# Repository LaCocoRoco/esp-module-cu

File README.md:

# Control Unit

Receiver to control onbaoard relays.

## Quick Guide

1. Order PCB by uploading the [Gerber File](pcb/cam/esp-module-cu.zip) to [JLCPCB](https://jlcpcb.com/).
2. Order Parts by uploading the [BOM File](pcb/bom/esp-module-cu.csv) to [LCSC](https://www.lcsc.com/bom).
3. Build PCB by placing components as visualized in the [BOM Viewer](https://htmlpreview.github.io/?https://github.com/LaCocoRoco/esp-module-cu/blob/main/pcb/bom/esp-module-cu.html).
4. Download & Install [Git](https://git-scm.com/), [CP210x Driver](https://www.silabs.com/developers/usb-to-uart-bridge-vcp-drivers?tab=downloads) and [VSCode](https://code.visualstudio.com/) with [PlatformIO](https://platformio.org/) Extension.
5. Clone the Repository `git clone --recursive https://github.com/LaCocoRoco/esp-module-cu.git`.
6. Customize your desired behaviour in [io.cpp](https://github.com/LaCocoRoco/esp-module-codebase/blob/main/src/io.cpp) or use the existing code from the [home](https://github.com/LaCocoRoco/esp-module-codebase/tree/home) branche.
7. With PlatformIO `Upload Filsystem Image` & `Upload & Monitor ` to your board.

## Module Modes

Modes can be changed by pressing the mode button.  
An audio signal will provide feedback for the active mode.  
Holding the mode button for more than two seconds will clear the module.

### Low Power Mode

- Feedback with one audio signal
- All web functionality is disabled
- Device will enter deep sleep when inactive
- Battery lifetime of several months

### Hybrid Mode

- Feedback with two audio signals
- All web functionality is disabled
- Device will enter deep sleep when battery voltage is below 3.8V
- Battery lifetime of several days

### Web Mode

- Feedback with three audio signals
- All web functionality is enabled
- Battery lifetime of several hours

## Importend

All modules have three different modes: Web Mode, Hybrid Mode, and Low Power Mode.  
The Wi-Fi can be configured as either Access Point or Station Mode.  
However, due to the use of the EspNow protocol for communication, there are some restrictions.

### Modules Set Up as Access Points (Default):

- All modes work without any restrictions.

### Modules Set Up in Station Mode:

- Web Mode works without any restrictions.
- Low Power Mode and Hybrid Mode only work if the Wi-Fi network is set to a **fixed channel**.

### Modules Set Up in Access Point or Station Mode:

- All modes only work if the Wi-Fi network is set to **channel 1**.

## Explanation

The main goal of this project was to avoid reliance on any infrastructure. For configuration, neither an application nor an existing Wi-Fi network is necessary. All modules can be accessed via the corresponding SSID in Access Point Mode or via hostname in Station Mode. However, there are some trade-offs:

To reduce power consumption in Low Power Mode, the module does not establish a direct network connection. It only broadcasts data to the specified receiver. In Station Mode, the network may change the Wi-Fi channel occasionally. Connecting to the network to receive this information would significantly increase uptime.

An alternative approach to this problem would be to scan for the receiver and request the channel. However, this has additional drawbacks:

- Scanning for this information takes some time (though less compared to connecting to a Wi-Fi network).
- It is difficult to distinguish whether a transmission failure is due to the wrong channel or a general network issue.
- Continuously requesting this information until a response is received would quickly add to the uptime and increase power consumption.

This is the reason why the relevant points must be considered mentioned in the [Importand](#importend) section.

## Reference

- [VSCode](https://code.visualstudio.com/) - Lightweight code editor.
- [PlatformIO](https://platformio.org/) - Embedded software development gateway.
- [Autodesk Fusion 360](https://www.autodesk.com/products/fusion-360) - Design and manufacturing software for CAD, CAM, CAE, and PCB.
- [Autodesk Eagle](https://www.autodesk.com/products/eagle) - Electronic design automation software for printed circuit boards.
- [JLCPCB](https://jlcpcb.com/) - Reasonably priced PCB manufacturer.
- [LCSC](https://www.lcsc.com/) - Supplier for a wide selection of electronic components.
- [CP210x Driver](https://www.silabs.com/developers/usb-to-uart-bridge-vcp-drivers?tab=downloads) - USB to UART Driver for uploading codebase.
- [InteractiveHtmlBom](https://github.com/openscopeproject/InteractiveHtmlBom) - Bill of materials listing to visually search for components and their placements.

## Preview

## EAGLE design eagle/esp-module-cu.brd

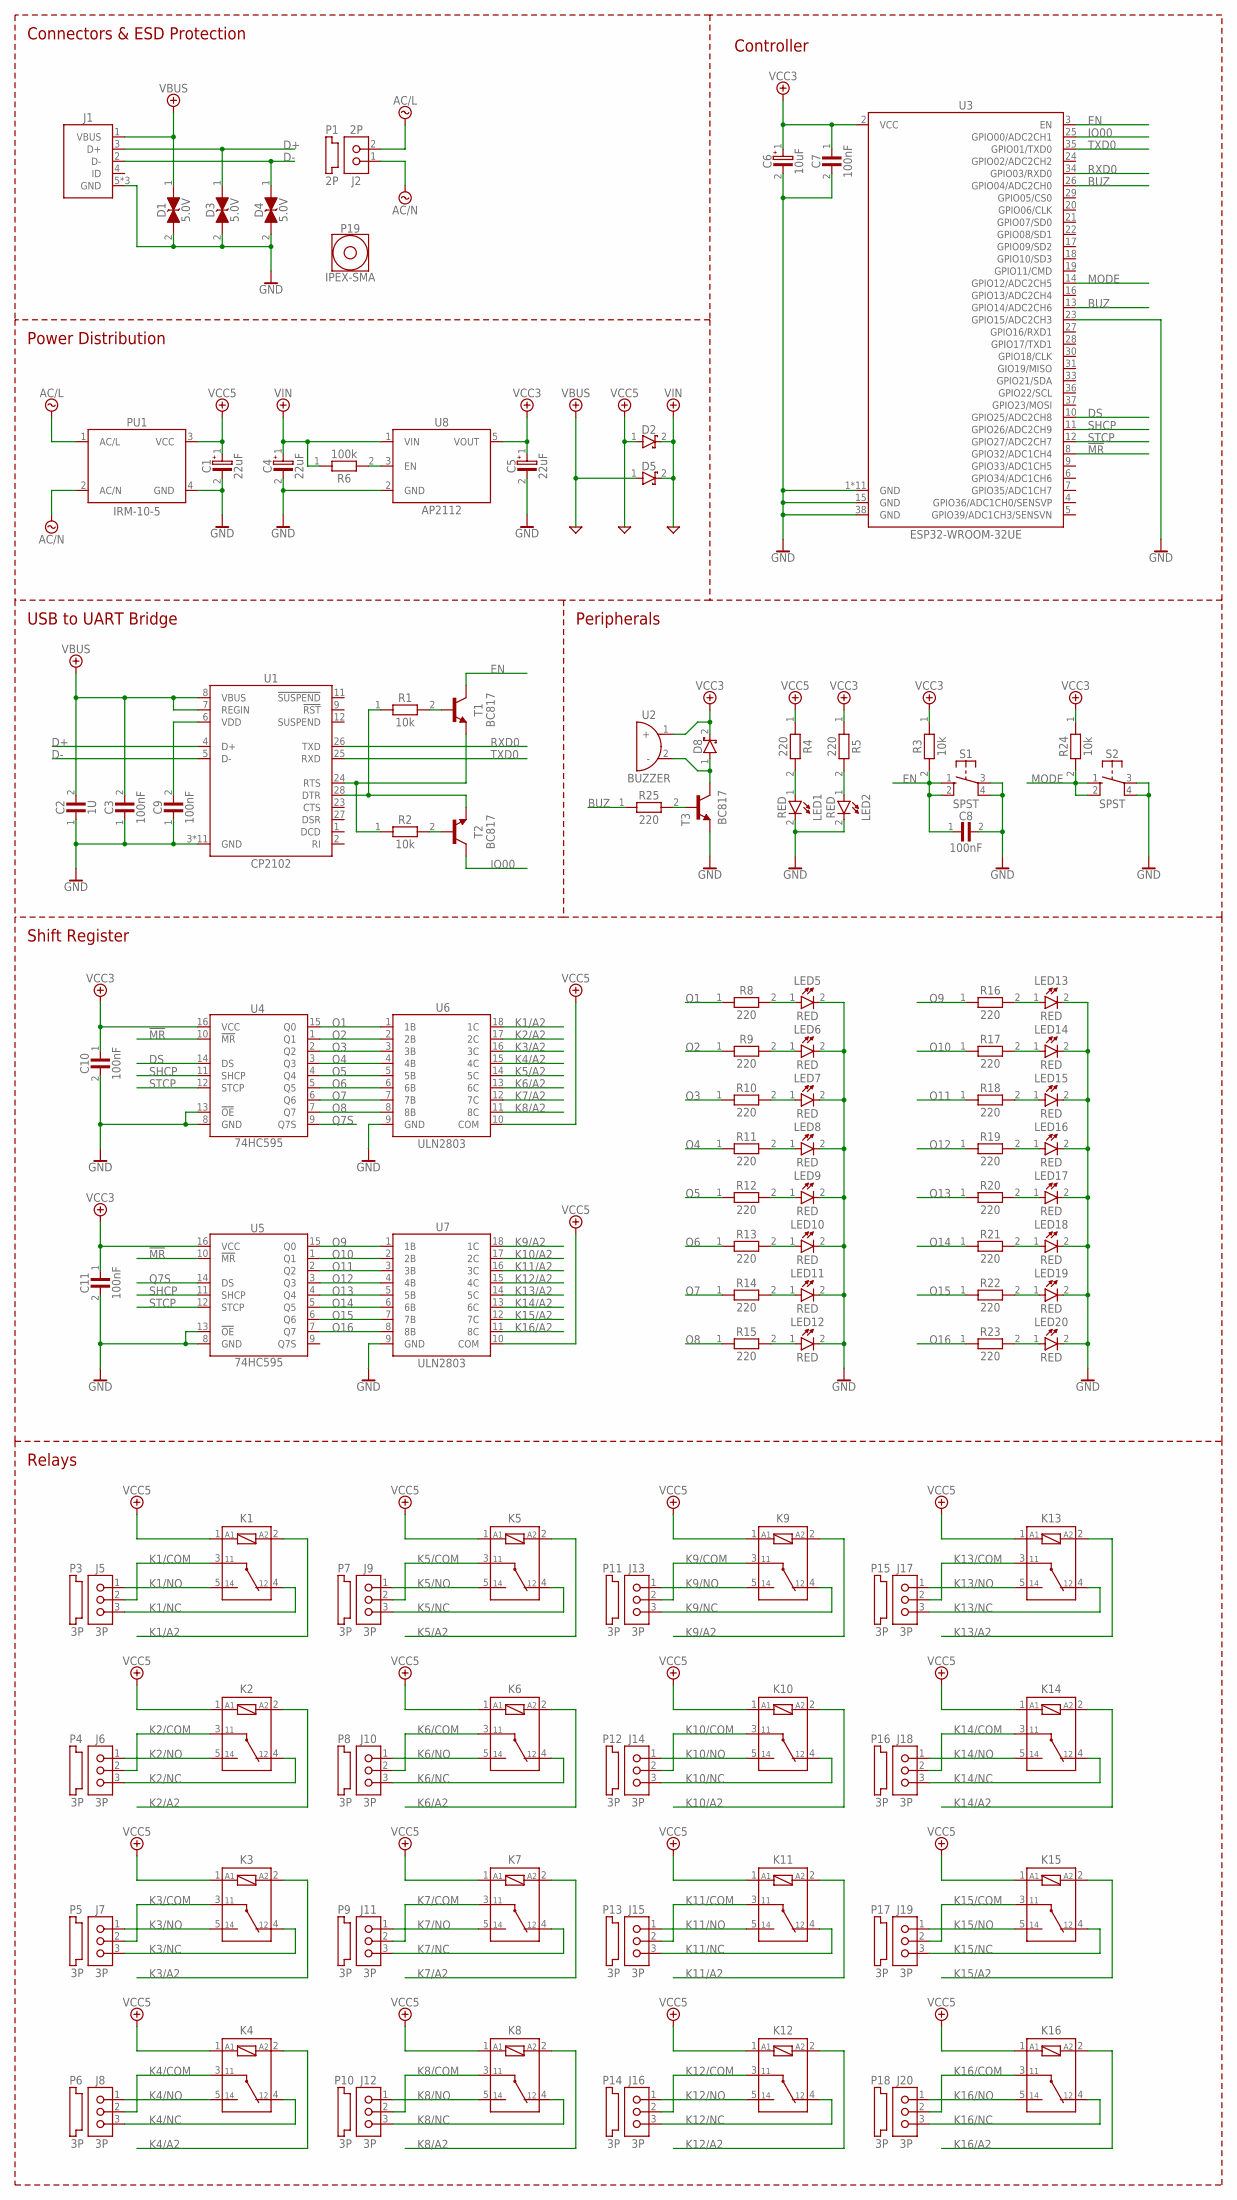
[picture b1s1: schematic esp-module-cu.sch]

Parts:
C1, C4, C5: 22uF; I1206-M3216-D
C2: 1U; I0805-M2012-C
C3, C7, C8, C9, C10, C11: 100nF; I0805-M2012-C
C6: 10uF; I1206-M3216-D
D1, D3, D4: 5.0V; SOD-523
D2, D5, D8: 30V; SOD-323
J1: USB-A-MICRO-TOP
J2: 2P; KF2EDGV-5.08-2P
J5, J6, J7, J8, J9, J10, J11, J12, J13, J14, J15, J16, J17, J18, J19, J20: 3P; KF2EDGV-5.08-3P
K1, K2, K3, K4, K5, K6, K7, K8, K9, K10, K11, K12, K13, K14, K15, K16: 5V; SRD
LED1, LED2, LED5, LED6, LED7, LED8, LED9, LED10, LED11, LED12, LED13, LED14, LED15, LED16, LED17, LED18, LED19, LED20: RED; I0805-M2012-D
P1: 2P; CONNECTOR-DEFAULT
P3, P4, P5, P6, P7, P8, P9, P10, P11, P12, P13, P14, P15, P16, P17, P18: 3P; CONNECTOR-DEFAULT
P19: IPEX-SMA; SMA
PU1: IRM-10-5; IRM-10
R1, R2, R3, R24: 10k; I0805-M2012-R
R4, R5, R8, R9, R10, R11, R12, R13, R14, R15, R16, R17, R18, R19, R20, R21, R22, R23, R25: 220; I0805-M2012-R
R6: 100k; I0805-M2012-R
S1, S2: SPST; SMD-SW-4
T1, T2, T3: BC817; SOT-23-3
U1: CP2102; QFN-28
U2: BUZZER; SMD-BUZZER
U3: ESP32-WROOM-32UE
U4, U5: 74HC595; SOIC-16
U6, U7: ULN2803; SOIC-18
U8: AP2112; SOT-25-5

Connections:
!MR: U3.8 (GPIO32/ADC1CH4), U4.10 (!MR), U5.10 (!MR)
APEN: R6.2, U8.3 (EN)
BUZ: R25.1, U3.13 (GPIO14/ADC2CH6), U3.26 (GPIO04/ADC2CH0)
BZB: R25.2, T3.1 (B)
BZC: D8.1 (A), T3.3 (C), U2.2 (-)
D+: D3.1 (A), J1.3 (D+), U1.4 (D+)
D-: D4.1 (A), J1.2 (D-), U1.5 (D-)
DS: U3.10 (GPIO25/ADC2CH8), U4.14 (DS)
DTR1: R1.1, T2.2 (E), U1.28 (DTR)
DTRT1: R1.2, T1.1 (B)
EN: C8.1, R3.2, S1.1, S1.2, T1.3 (C), U3.3 (EN)
GND: C1.2 (-), C2.1, C3.1, C4.2 (-), C5.2 (-), C6.2 (-), C7.2, C8.2, C9.1, C10.2, C11.2, D1.2 (C), D3.2 (C), D4.2 (C), J1.5 (GND), J1.6 (GND), J1.7 (GND), LED1.2 (C), LED2.2 (C), LED5.2 (C), LED6.2 (C), LED7.2 (C), LED8.2 (C), LED9.2 (C), LED10.2 (C), LED11.2 (C), LED12.2 (C), LED13.2 (C), LED14.2 (C), LED15.2 (C), LED16.2 (C), LED17.2 (C), LED18.2 (C), LED19.2 (C), LED20.2 (C), PU1.4 (GND), S1.3, S1.4, S2.3, S2.4, T3.2 (E), U1.3 (GND), U1.29 (GND), U1.30 (GND), U1.31 (GND), U1.32 (GND), U1.33 (GND), U1.34 (GND), U1.35 (GND), U1.36 (GND), U1.37 (GND), U1.38 (GND), U3.1 (GND), U3.15 (GND), U3.23 (GPIO15/ADC2CH3), U3.38 (GND), U3.39 (GND), U3.40 (GND), U3.41 (GND), U3.42 (GND), U3.43 (GND), U3.44 (GND), U3.45 (GND), U3.46 (GND), U3.47 (GND), U3.48 (GND), U4.8 (GND), U4.13 (!OE), U5.8 (GND), U5.13 (!OE), U6.9 (GND), U7.9 (GND), U8.2 (GND)
IO00: T2.3 (C), U3.25 (GPIO00/ADC2CH1)
K1/A2: K1.2 (A2), U6.18 (1C)
K1/COM: J5.2, K1.3 (11)
K1/NC: J5.3, K1.4 (12)
K1/NO: J5.1, K1.5 (14)
K1LED: LED5.1 (A), R8.2
K2/A2: K2.2 (A2), U6.17 (2C)
K2/COM: J6.2, K2.3 (11)
K2/NC: J6.3, K2.4 (12)
K2/NO: J6.1, K2.5 (14)
K2LED1: LED6.1 (A), R9.2
K3/A2: K3.2 (A2), U6.16 (3C)
K3/COM: J7.2, K3.3 (11)
K3/NC: J7.3, K3.4 (12)
K3/NO: J7.1, K3.5 (14)
K3LED1: LED7.1 (A), R10.2
K4/A2: K4.2 (A2), U6.15 (4C)
K4/COM: J8.2, K4.3 (11)
K4/NC: J8.3, K4.4 (12)
K4/NO: J8.1, K4.5 (14)
K4LED1: LED8.1 (A), R11.2
K5/A2: K5.2 (A2), U6.14 (5C)
K5/COM: J9.2, K5.3 (11)
K5/NC: J9.3, K5.4 (12)
K5/NO: J9.1, K5.5 (14)
K5LED1: LED9.1 (A), R12.2
K6/A2: K6.2 (A2), U6.13 (6C)
K6/COM: J10.2, K6.3 (11)
K6/NC: J10.3, K6.4 (12)
K6/NO: J10.1, K6.5 (14)
K6LED1: LED10.1 (A), R13.2
K7/A2: K7.2 (A2), U6.12 (7C)
K7/COM: J11.2, K7.3 (11)
K7/NC: J11.3, K7.4 (12)
K7/NO: J11.1, K7.5 (14)
K7LED1: LED11.1 (A), R14.2
K8/A2: K8.2 (A2), U6.11 (8C)
K8/COM: J12.2, K8.3 (11)
K8/NC: J12.3, K8.4 (12)
K8/NO: J12.1, K8.5 (14)
K8LED1: LED12.1 (A), R15.2
K9/A2: K9.2 (A2), U7.18 (1C)
K9/COM: J13.2, K9.3 (11)
K9/NC: J13.3, K9.4 (12)
K9/NO: J13.1, K9.5 (14)
K09LED: LED13.1 (A), R16.2
K10/A2: K10.2 (A2), U7.17 (2C)
K10/COM: J14.2, K10.3 (11)
K10/NC: J14.3, K10.4 (12)
K10/NO: J14.1, K10.5 (14)
K10LED: LED14.1 (A), R17.2
K11/A2: K11.2 (A2), U7.16 (3C)
K11/COM: J15.2, K11.3 (11)
K11/NC: J15.3, K11.4 (12)
K11/NO: J15.1, K11.5 (14)
K11LED: LED15.1 (A), R18.2
K12/A2: K12.2 (A2), U7.15 (4C)
K12/COM: J16.2, K12.3 (11)
K12/NC: J16.3, K12.4 (12)
K12/NO: J16.1, K12.5 (14)
K12LED: LED16.1 (A), R19.2
K13/A2: K13.2 (A2), U7.14 (5C)
K13/COM: J17.2, K13.3 (11)
K13/NC: J17.3, K13.4 (12)
K13/NO: J17.1, K13.5 (14)
K13LED: LED17.1 (A), R20.2
K14/A2: K14.2 (A2), U7.13 (6C)
K14/COM: J18.2, K14.3 (11)
K14/NC: J18.3, K14.4 (12)
K14/NO: J18.1, K14.5 (14)
K14LED: LED18.1 (A), R21.2
K15/A2: K15.2 (A2), U7.12 (7C)
K15/COM: J19.2, K15.3 (11)
K15/NC: J19.3, K15.4 (12)
K15/NO: J19.1, K15.5 (14)
K15LED: LED19.1 (A), R22.2
K16/A2: K16.2 (A2), U7.11 (8C)
K16/COM: J20.2, K16.3 (11)
K16/NC: J20.3, K16.4 (12)
K16/NO: J20.1, K16.5 (14)
K16LED: LED20.1 (A), R23.2
L: J2.2, PU1.1 (AC/L)
MODE: R24.2, S2.1, S2.2, U3.14 (GPIO12/ADC2CH5)
N: J2.1, PU1.2 (AC/N)
O1: R8.1, U4.15 (Q0), U6.1 (1B)
O2: R9.1, U4.1 (Q1), U6.2 (2B)
O3: R10.1, U4.2 (Q2), U6.3 (3B)
O4: R11.1, U4.3 (Q3), U6.4 (4B)
O5: R12.1, U4.4 (Q4), U6.5 (5B)
O6: R13.1, U4.5 (Q5), U6.6 (6B)
O7: R14.1, U4.6 (Q6), U6.7 (7B)
O8: R15.1, U4.7 (Q7), U6.8 (8B)
O9: R16.1, U5.15 (Q0), U7.1 (1B)
O10: R17.1, U5.1 (Q1), U7.2 (2B)
O11: R18.1, U5.2 (Q2), U7.3 (3B)
O12: R19.1, U5.3 (Q3), U7.4 (4B)
O13: R20.1, U5.4 (Q4), U7.5 (5B)
O14: R21.1, U5.5 (Q5), U7.6 (6B)
O15: R22.1, U5.6 (Q6), U7.7 (7B)
O16: R23.1, U5.7 (Q7), U7.8 (8B)
Q7S: U4.9 (Q7S), U5.14 (DS)
RTS1: R2.1, T1.2 (E), U1.24 (RTS)
RTST1: R2.2, T2.1 (B)
RXD0: U1.26 (TXD), U3.34 (GPIO03/RXD0)
SHCP: U3.11 (GPIO26/ADC2CH9), U4.11 (SHCP), U5.11 (SHCP)
STCP: U3.12 (GPIO27/ADC2CH7), U4.12 (STCP), U5.12 (STCP)
TXD0: U1.25 (RXD), U3.35 (GPIO01/TXD0)
VBUS: C2.2, C3.2, D1.1 (A), D5.1 (A), J1.1 (VBUS), U1.7 (REGIN), U1.8 (VBUS)
VCC3: C5.1 (+), C6.1 (+), C7.1, C10.1, C11.1, D8.2 (C), R3.1, R5.1, R24.1, U2.1 (+), U3.2 (VCC), U4.16 (VCC), U5.16 (VCC), U8.5 (VOUT)
VCC5: C1.1 (+), D2.1 (A), K1.1 (A1), K2.1 (A1), K3.1 (A1), K4.1 (A1), K5.1 (A1), K6.1 (A1), K7.1 (A1), K8.1 (A1), K9.1 (A1), K10.1 (A1), K11.1 (A1), K12.1 (A1), K13.1 (A1), K14.1 (A1), K15.1 (A1), K16.1 (A1), PU1.3 (VCC), R4.1, U6.10 (COM), U7.10 (COM)
VCCLED1: LED2.1 (A), R5.2
VCCLED2: LED1.1 (A), R4.2
VDD: C9.2, U1.6 (VDD)
VIN: C4.1 (+), D2.2 (C), D5.2 (C), R6.1, U8.1 (VIN)

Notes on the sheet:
Peripherals
Controller
Shift Register
Power Distribution
USB to UART Bridge
Relays
Connectors & ESD Protection

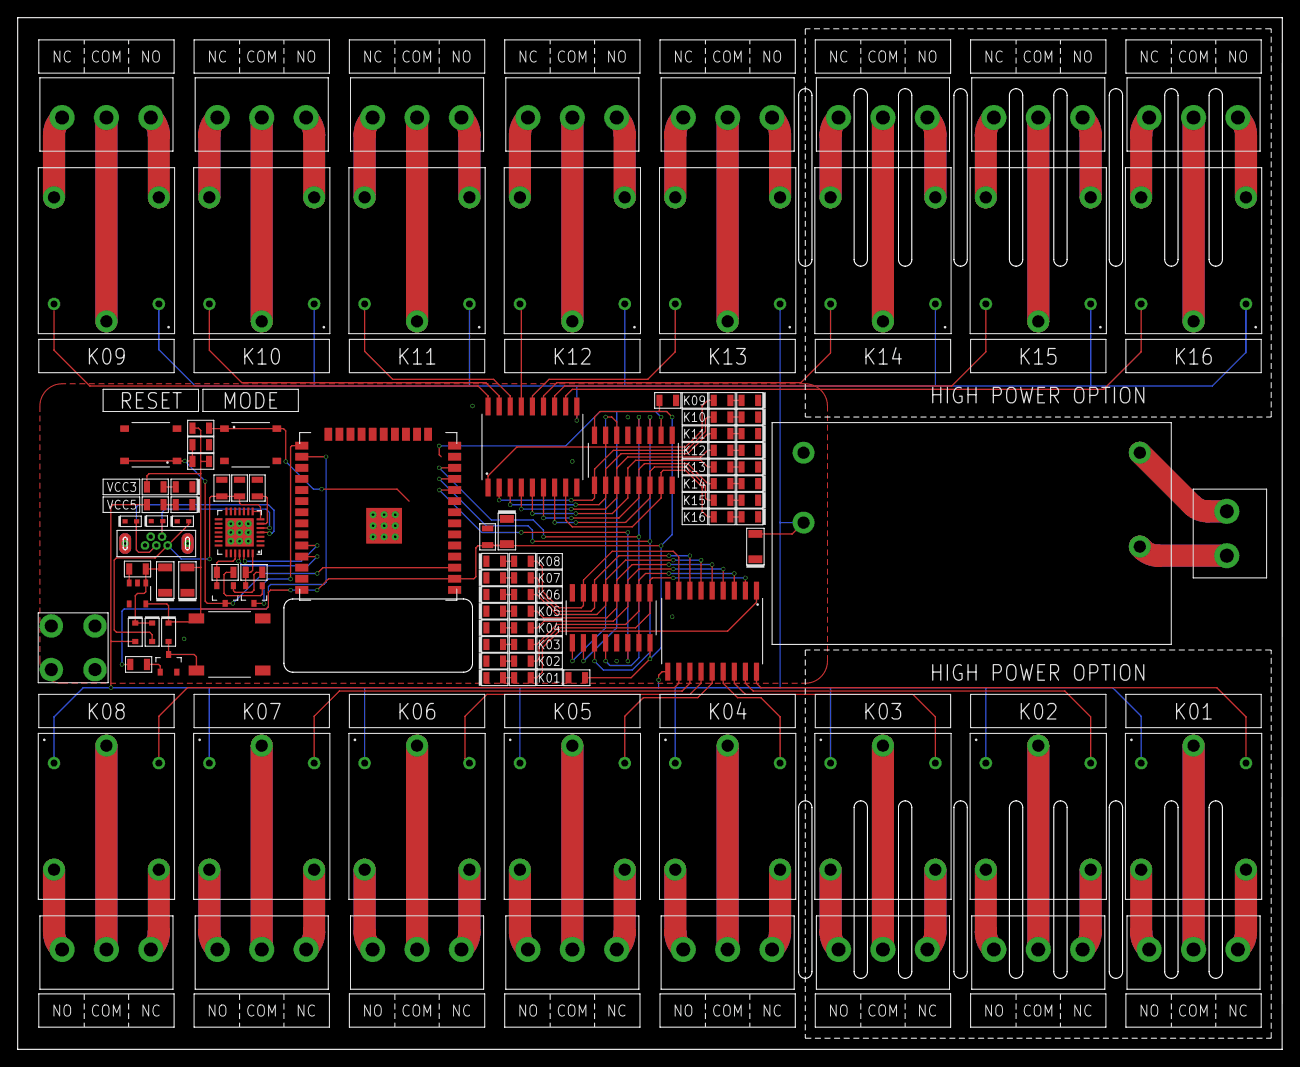
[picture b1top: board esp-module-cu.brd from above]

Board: 2 copper layers, 144.8 x 118.1 mm, 125 parts (0 on the bottom side), 126 nets.

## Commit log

2024-06-26 Inititial Commit
2024-06-29 UpdateUpdate
